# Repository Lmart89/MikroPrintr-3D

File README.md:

# MikroPrinter-3D.
## Una placa controladora de impresion 3d de bajo coste basada en Arduino.

## 💡 Origen del Concepto

Mikropintr es el resultado propio de ideas tomadas de proyectos como Sinaptec (https://reprap.org/wiki/SinapTec), Morpheus (https://github.com/pscrespo/Morpheus-STM32) entre otros que ofrecen una solucion compacta y de bajo coste para la construccion de una placa controladora de impresion 3D. Sin embargo el gran limitante de estas placas es la necesidad de modificar el firmware para lograr compatiblidad con estos dispositovos, algo que requiere de mucho trabajo mas alla de la personalizacion, sin contar con los bugs resultantes en el proceso.
MikroPrintr pretende ofrecer una solucion asequible, a la vez de ser 100% compatible con Marlin, permitiendo desarrollar todo el potencial y la personalizacion a gusto. Para quepueda ser una placa compacta se opto por el arduino mega 2560 pro, una version reducida de Arduino Mega.

## :heavy_check_mark: Características de MikroPrintr.

- MCU: Arduino Mega 2560 Pro-Micro. Un Arduino Mega reducido en tamaño.

- Soporte Estándar de Marlin 2.0

- Diseñada bajo el standar RAMPS 1.4.

- Fabricación para uso de componentes THT (Trough Hole). 

- Tamaño Reducido. 103 mm x 90mm. a 1 sola capa, o producir a dos capas si se desea.

- Soporte Estándar de la smart reprap controller (lcd 2004) o la smart reprap full graphic controller (lcd 12864). no necesita la placa adaptadora para la conexion.
  
- Soporte para Módulo Wifi (esp8266-01 o esp8266-01s) Se recomienda la versión Esp-01s. se requiere un regulador de nivel lógico de 5v a 3.3V.

## :chart_with_upwards_trend: Estado del Proyecto.

:construction: Proyecto en construcción :construction:

## :books: Registro de cambios

###  Abril 2025.
- Se optimizo el diseño de la placa, y se corrigieron algunos detalles menores de la circuiteria.
- Rediseño de las piezas de la impresora con nuevas medidas, por un error de medicion en algunas de ellas.
- se libera la version 1H. de la placa.  

## :books: Recursos adicionales.

los siguientes modelos de impresoras pueden dar una fuente de inspiracion para el montaje  o diseño de una impresora 3d. uselos segun discrecion y precaucion propias.

### Me Mini 3d Printer - la mas completa y compleja.

:earth_americas: link oficial. https://www.thingiverse.com/thing:5140212. 

### Skylab2 - una construccion sencilla y simple, recomendada para empezar. 

:earth_americas: link oficial. https://www.thingiverse.com/thing:4624533.

### Prusa mini- la version mini de la prusa i3.
   Requiere la mayoria de sus piezas en ABS. 

🌎 sitio oficial: https://www.printables.com/es/model/57214-mini-printable-parts/files

los archivos stl de estos modelos se encuentran en la carpeta "printable parts".

## :hammer_and_pick: Proyectos en conjunto. 
De momento estoy trabajando en el desarrollo de un software host propio para manejar la placa.

Si te interesa mi proyecto y deseas colaborar en el desarrollo, puedes contactarme, dejandome un mensaje o un request o solicitud de cambio via github.

Deseo que este proyecto pueda ser de utilidad para ti, maker. con :heart: desde Colombia 🇨🇴 para el mundo 🌎. :smile:

### <h4> :heavy_exclamation_mark: al hacer uso de los archivos publicados en este repositorio, el usuario acepta y asume su propia responsabilidad y riesgo por el uso y/o manipulacion de los archivos ofrecidos en este repositorio. :heavy_exclamation_mark: </h>

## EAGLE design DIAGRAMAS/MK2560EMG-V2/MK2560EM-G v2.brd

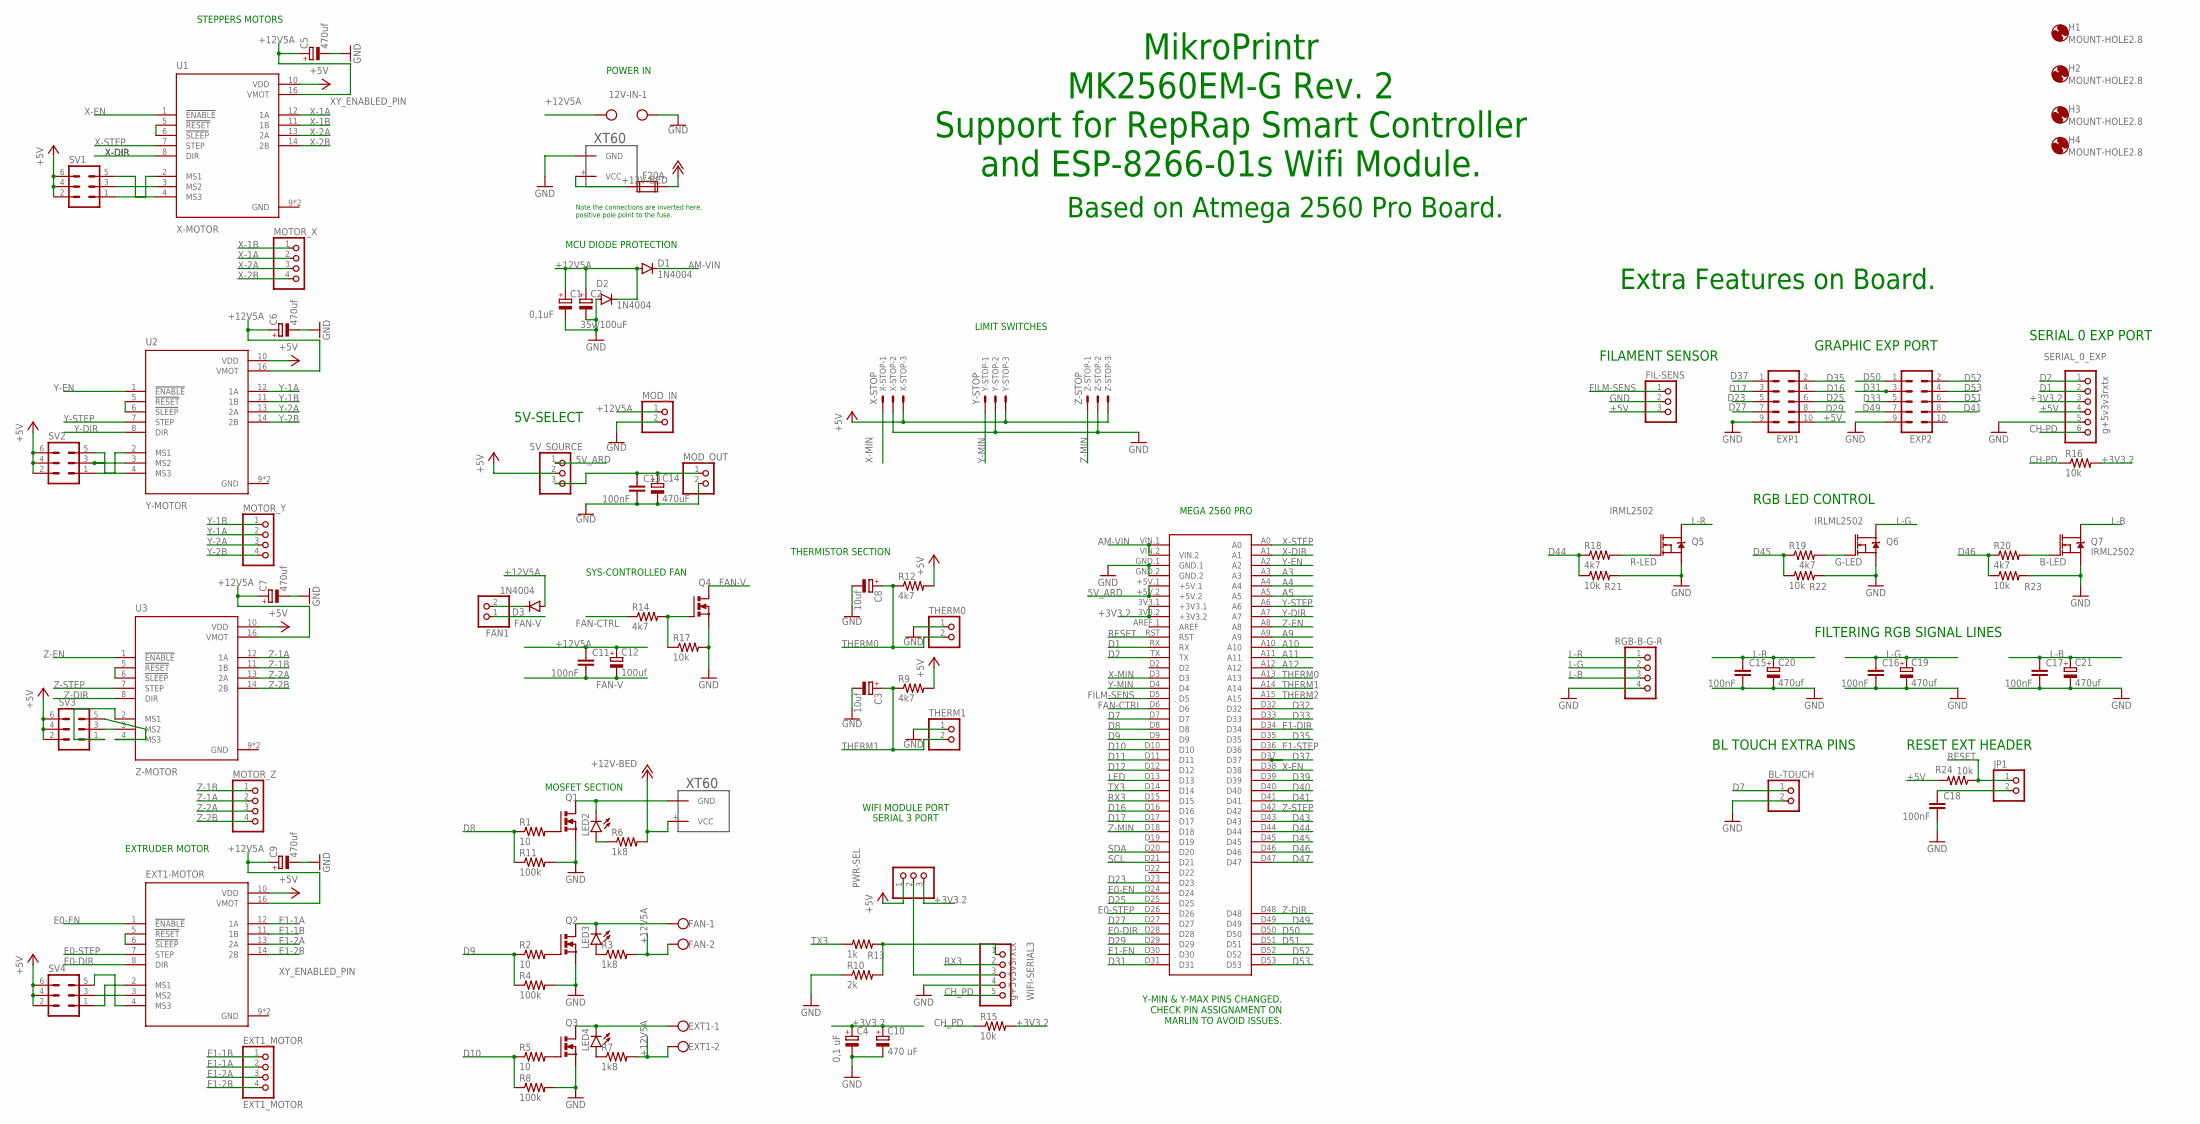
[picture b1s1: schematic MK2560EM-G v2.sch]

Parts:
5V_SOURCE: PINHD-1X3; 1X03
12V-IN: W237-102
ARD-MEGA: MEGA2560_MIKRO
BL-TOUCH: PINHD-1X2; 1X02
C1: 0,1uF; E2,5-5
C2: 35v/100uF; E2,5-5
C3, C8: 10uf; E2,5-6
C4: 0,1 uF; E2,5-5
C5, C6, C7, C9, C19, C20, C21: 470uf; E2,5-6E
C10: 470 uF; E2,5-5
C11, C13, C15, C16, C17, C18: 100nF; C2.5-2
C12: 100uf; E2,5-6
C14: 470uF; E2,5-6
D1, D2, D3: 1N4004; DO41-10
EXP1, EXP2: MA05-2
EXT1: W237-102
EXT1-MOTOR: A4988_STEPPER_MOTOR_DRIVER_CARRIER; MODULE_A4988_STEPPER_MOTOR_DRIVER_CARRIER
EXT1_MOTOR: EXT1_MOTOR; 1X04
F20A: FUSE2P; FUSE1
FAN: W237-102
FAN1: PINHD-1X2; 1X02
FIL-SENS: PINHD-1X3; 1X03
H1, H2, H3, H4: MOUNT-HOLE2.8; 2,8
JP1: PINHD-1X2; 1X02
LED2, LED3, LED4: LED3MM
MOD_IN: PINHD-1X2; 1X02
MOD_OUT: PINHD-1X2; 1X02
MOTOR_X: PINHD-1X4; 1X04
MOTOR_Y: PINHD-1X4; 1X04
MOTOR_Z: PINHD-1X4; 1X04
PWR-SEL: PINHD-1X3; 1X03
Q1, Q2, Q3, Q4: PMOSFET_NTO220BV; TO220BV
Q5, Q7: IRML2502; SOT23-3
Q6: IRLML2502; SOT23-3
R1, R2, R5: 10; 0204/7
R3, R6, R7: 1k8; 0204/7
R4, R8, R11: 100k; 0204/7
R9, R12, R14, R18, R19, R20: 4k7; 0204/7
R10: 2k; 0204/7
R13: 1k; 0204/7
R15, R16, R17, R21, R22, R23, R24: 10k; 0204/7
RGB-B-G-R: PINHD-1X4; 1X04
SERIAL_0_EXP: g+5v3v3rxtx; 1X06
SV1, SV2, SV3, SV4: MA03-2
THERM0, THERM1: PINHD-1X2; 1X02
U1: X-MOTOR; MODULE_A4988_STEPPER_MOTOR_DRIVER_CARRIER
U2: Y-MOTOR; MODULE_A4988_STEPPER_MOTOR_DRIVER_CARRIER
U3: Z-MOTOR; MODULE_A4988_STEPPER_MOTOR_DRIVER_CARRIER
U$1, U$2: XT60
WIFI-SERIAL3: g+5v3v3rxtx; 1X05
X-STOP: X-STOP; 22-23-2031
Y-STOP: Y-STOP; 22-23-2031
Z-STOP: Z-STOP; 22-23-2031

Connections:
5V_ARD: 5V_SOURCE.1, ARD-MEGA.+5V.1, ARD-MEGA.+5V.2
+3V3.2: ARD-MEGA.3V3.1 (+3V3.1), ARD-MEGA.3V3.2 (+3V3.2), C4.+, C10.+, PWR-SEL.3, R15.2, R16.2, SERIAL_0_EXP.3
+5V: 5V_SOURCE.2, EXP1.10, EXT1-MOTOR.10 (VDD), FIL-SENS.3, PWR-SEL.1, R9.2, R12.2, R24.2, SERIAL_0_EXP.4, SV1.2, SV1.4, SV1.6, SV2.2, SV2.4, SV2.6, SV3.2, SV3.4, SV3.6, SV4.2, SV4.4, SV4.6, U1.10 (VDD), U2.10 (VDD), U3.10 (VDD), X-STOP.3, Y-STOP.3, Z-STOP.3
+12V: F20A.2A, R6.2, U$2.+ (VCC)
+12V5A: 12V-IN.2, C1.+, C2.+, C5.+, C6.+, C7.+, C9.+, C11.1, C12.+, D1.A, D2.C, D3.A, EXT1.2, EXT1-MOTOR.16 (VMOT), FAN.2, MOD_IN.1, R3.2, R7.2, U1.16 (VMOT), U2.16 (VMOT), U3.16 (VMOT)
A3: ARD-MEGA.A3
A4: ARD-MEGA.A4
A5: ARD-MEGA.A5
A9: ARD-MEGA.A9
A10: ARD-MEGA.A10
A11: ARD-MEGA.A11
A12: ARD-MEGA.A12
AM-VIN: ARD-MEGA.VIN.1, ARD-MEGA.VIN.2, D1.C
B-LED: Q7.1 (G), R20.2
CH-PD: R16.1, SERIAL_0_EXP.6
CH_PD: R15.1, WIFI-SERIAL3.5
D1: ARD-MEGA.RX, SERIAL_0_EXP.2
D2: ARD-MEGA.TX, SERIAL_0_EXP.1
D7: ARD-MEGA.D7, BL-TOUCH.1
D8: ARD-MEGA.D8, R1.1, R11.1
D9: ARD-MEGA.D9, R2.1, R4.1
D10: ARD-MEGA.D10, R5.1, R8.1
D11: ARD-MEGA.D11
D12: ARD-MEGA.D12
D16: ARD-MEGA.D16, EXP1.4
D17: ARD-MEGA.D17, EXP1.3
D23: ARD-MEGA.D23, EXP1.5
D25: ARD-MEGA.D25, EXP1.6
D27: ARD-MEGA.D27, EXP1.7
D29: ARD-MEGA.D29, EXP1.8
D31: ARD-MEGA.D31, EXP2.3
D32: ARD-MEGA.D32
D33: ARD-MEGA.D33, EXP2.5
D35: ARD-MEGA.D35, EXP1.2
D37: ARD-MEGA.D37, EXP1.1
D39: ARD-MEGA.D39
D40: ARD-MEGA.D40
D41: ARD-MEGA.D41, EXP2.8
D43: ARD-MEGA.D43
D44: ARD-MEGA.D44, R18.1, R21.1
D45: ARD-MEGA.D45, R19.1, R22.1
D46: ARD-MEGA.D46, R20.1, R23.1
D47: ARD-MEGA.D47
D49: ARD-MEGA.D49, EXP2.7
D50: ARD-MEGA.D50, EXP2.1
D51: ARD-MEGA.D51, EXP2.6
D52: ARD-MEGA.D52, EXP2.2
D53: ARD-MEGA.D53, EXP2.4
E0-DIR: ARD-MEGA.D28, EXT1-MOTOR.8 (DIR)
E0-EN: ARD-MEGA.D24, EXT1-MOTOR.1 (!ENABLE)
E0-STEP: ARD-MEGA.D26, EXT1-MOTOR.7 (STEP)
E1-1A: EXT1-MOTOR.12 (1A), EXT1_MOTOR.2
E1-1B: EXT1-MOTOR.11 (1B), EXT1_MOTOR.1
E1-2A: EXT1-MOTOR.13 (2A), EXT1_MOTOR.3
E1-2B: EXT1-MOTOR.14 (2B), EXT1_MOTOR.4
E1-DIR: ARD-MEGA.D34
E1-EN: ARD-MEGA.D30
E1-STEP: ARD-MEGA.D36
FAN-CTRL: ARD-MEGA.D6, R14.1
FAN-V: C11.2, C12.-, FAN1.1, Q4.D
FILM-SENS: ARD-MEGA.D5, FIL-SENS.1
G-LED: Q6.1 (G), R19.2
GND: 12V-IN.1, ARD-MEGA.GND.1, ARD-MEGA.GND.2, BL-TOUCH.2, C1.-, C2.-, C3.-, C4.-, C5.-, C6.-, C7.-, C8.-, C9.-, C10.-, C13.2, C14.-, C15.2, C16.2, C17.2, C18.2, C19.-, C20.-, C21.-, D2.A, EXP1.9, EXP2.9, EXT1-MOTOR.9 (GND), EXT1-MOTOR.15 (GND), FIL-SENS.2, MOD_IN.2, MOD_OUT.2, Q1.S, Q2.S, Q3.S, Q4.S, Q5.2 (S), Q6.2 (S), Q7.2 (S), R4.2, R8.2, R10.1, R11.2, R17.2, R21.2, R22.2, R23.2, RGB-B-G-R.4, SERIAL_0_EXP.5, THERM0.1, THERM1.1, U1.9 (GND), U1.15 (GND), U2.9 (GND), U2.15 (GND), U3.9 (GND), U3.15 (GND), U$1.- (GND), WIFI-SERIAL3.4, X-STOP.2, Y-STOP.2, Z-STOP.2
L-B: C17.1, C21.+, Q7.3 (D), RGB-B-G-R.3
L-G: C16.1, C19.+, Q6.3 (D), RGB-B-G-R.2
L-R: C15.1, C20.+, Q5.3 (D), RGB-B-G-R.1
LED: ARD-MEGA.D13
unnamed: Q2.G, R2.2
unnamed: FAN.1, LED3.K (C), Q2.D
unnamed: LED3.A, R3.1
unnamed: Q3.G, R5.2
unnamed: EXT1.1, LED4.K (C), Q3.D
unnamed: LED4.A, R7.1
unnamed: LED2.K (C), Q1.D, U$2.- (GND)
unnamed: LED2.A, R6.1
unnamed: SV1.5, U1.4 (MS3)
unnamed: SV1.3, U1.3 (MS2)
unnamed: SV1.1, U1.2 (MS1)
unnamed: U2.5 (!RESET), U2.6 (!SLEEP)
unnamed: U1.5 (!RESET), U1.6 (!SLEEP)
unnamed: SV2.1, U2.2 (MS1)
unnamed: SV2.3, U2.3 (MS2)
unnamed: SV2.5, U2.4 (MS3)
unnamed: U3.5 (!RESET), U3.6 (!SLEEP)
unnamed: R10.2, R13.2, WIFI-SERIAL3.1
unnamed: SV3.3, U3.3 (MS2)
unnamed: Q1.G, R1.2
unnamed: SV3.1, U3.2 (MS1)
unnamed: SV3.5, U3.4 (MS3)
unnamed: EXT1-MOTOR.5 (!RESET), EXT1-MOTOR.6 (!SLEEP)
unnamed: EXT1-MOTOR.3 (MS2), SV4.3
unnamed: EXT1-MOTOR.4 (MS3), SV4.5
unnamed: EXT1-MOTOR.2 (MS1), SV4.1
unnamed: Q4.G, R14.2, R17.1
unnamed: D3.C, FAN1.2
unnamed: F20A.1A, U$1.+ (VCC)
unnamed: 5V_SOURCE.3, C13.1, C14.+, MOD_OUT.1
unnamed: PWR-SEL.2, WIFI-SERIAL3.3
unnamed: C18.1, JP1.2
R-LED: Q5.1 (G), R18.2
RESET: ARD-MEGA.RST, JP1.1, R24.1
RX3: ARD-MEGA.D15, WIFI-SERIAL3.2
SCL: ARD-MEGA.D21
SDA: ARD-MEGA.D20
THERM0: ARD-MEGA.A13, C8.+, R12.1, THERM0.2
THERM1: ARD-MEGA.A14, C3.+, R9.1, THERM1.2
THERM2: ARD-MEGA.A15
TX3: ARD-MEGA.D14, R13.1
X-1A: MOTOR_X.2, U1.12 (1A)
X-1B: MOTOR_X.1, U1.11 (1B)
X-2A: MOTOR_X.3, U1.13 (2A)
X-2B: MOTOR_X.4, U1.14 (2B)
X-DIR: ARD-MEGA.A1, U1.8 (DIR)
X-EN: ARD-MEGA.D38, U1.1 (!ENABLE)
X-MIN: ARD-MEGA.D3, X-STOP.1
X-STEP: ARD-MEGA.A0, U1.7 (STEP)
Y-1A: MOTOR_Y.2, U2.12 (1A)
Y-1B: MOTOR_Y.1, U2.11 (1B)
Y-2A: MOTOR_Y.3, U2.13 (2A)
Y-2B: MOTOR_Y.4, U2.14 (2B)
Y-DIR: ARD-MEGA.A7, U2.8 (DIR)
Y-EN: ARD-MEGA.A2, U2.1 (!ENABLE)
Y-MIN: ARD-MEGA.D4, Y-STOP.1
Y-STEP: ARD-MEGA.A6, U2.7 (STEP)
Z-1A: MOTOR_Z.2, U3.12 (1A)
Z-1B: MOTOR_Z.1, U3.11 (1B)
Z-2A: MOTOR_Z.3, U3.13 (2A)
Z-2B: MOTOR_Z.4, U3.14 (2B)
Z-DIR: ARD-MEGA.D48, U3.8 (DIR)
Z-EN: ARD-MEGA.A8, U3.1 (!ENABLE)
Z-MIN: ARD-MEGA.D18, Z-STOP.1
Z-STEP: ARD-MEGA.D42, U3.7 (STEP)

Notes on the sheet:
MikroPrintr MK2560EM-G Rev. 2 Support for RepRap Smart Controller and ESP-8266-01s Wifi Module.
Based on Atmega 2560 Pro Board.
Note the connections are inverted here. positive pole point to the fuse.
MCU DIODE PROTECTION
MOSFET SECTION
THERMISTOR SECTION
GRAPHIC EXP PORT
MEGA 2560 PRO
WIFI MODULE PORT
STEPPERS MOTORS
EXTRUDER MOTOR
LIMIT SWITCHES
SYS-CONTROLLED FAN
POWER IN
Y-MIN & Y-MAX PINS CHANGED. CHECK PIN ASSIGNAMENT ON MARLIN TO AVOID ISSUES.
5V-SELECT
SERIAL 3 PORT
SERIAL 0 EXP PORT
Extra Features on Board.
RGB LED CONTROL
FILTERING RGB SIGNAL LINES
FILAMENT SENSOR
RESET EXT HEADER
BL TOUCH EXTRA PINS

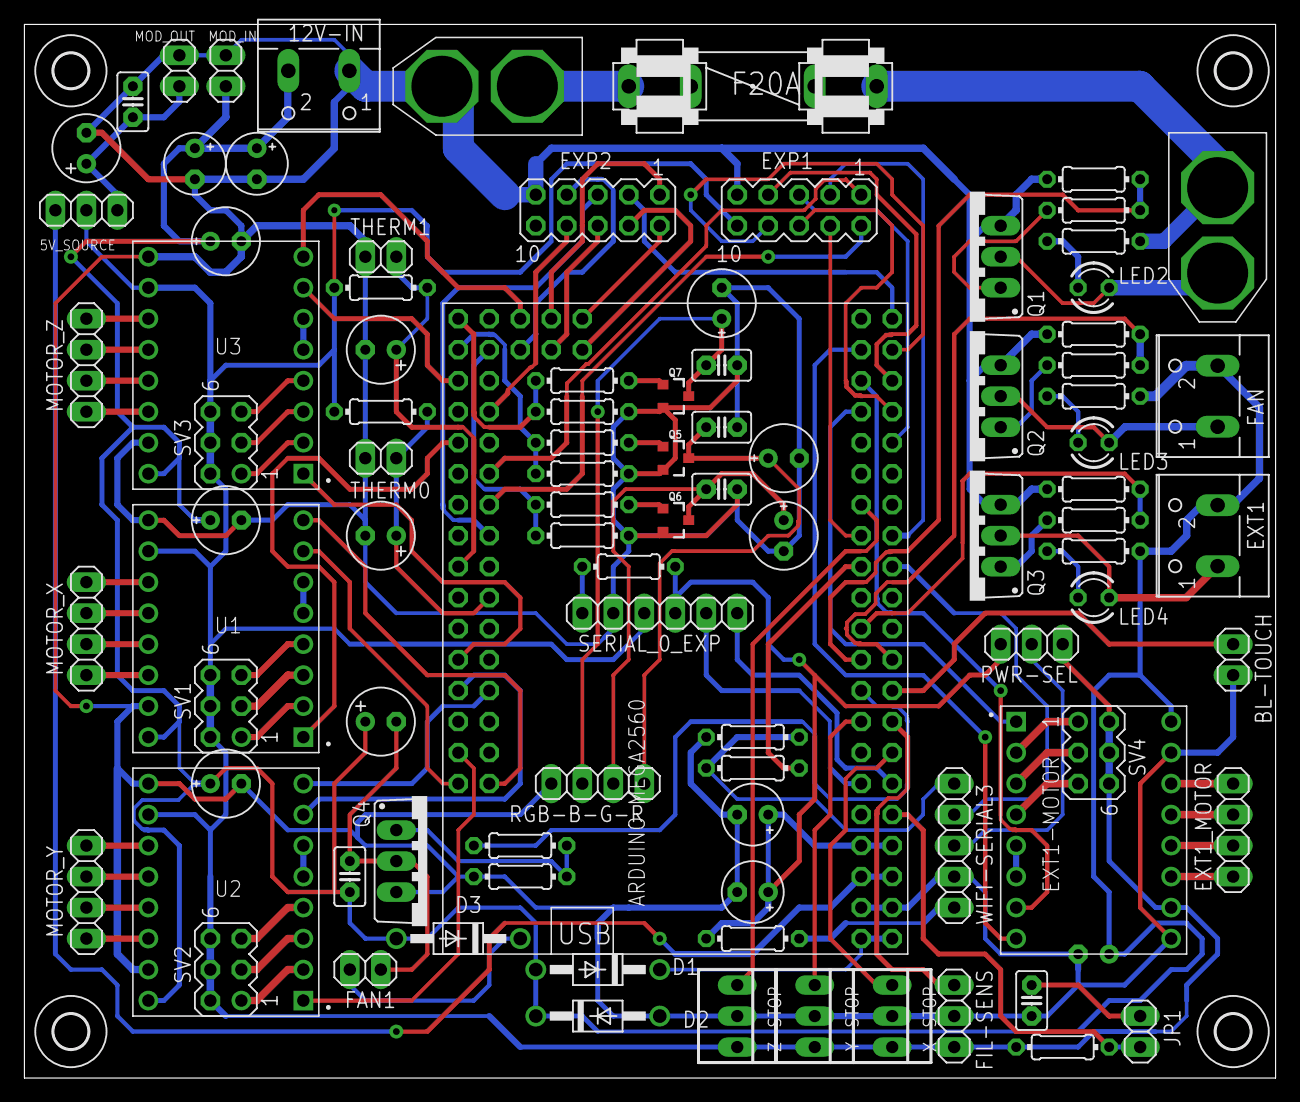
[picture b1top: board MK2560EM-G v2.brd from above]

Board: 2 copper layers, 102.5 x 86.4 mm, 99 parts (1 on the bottom side), 111 nets.

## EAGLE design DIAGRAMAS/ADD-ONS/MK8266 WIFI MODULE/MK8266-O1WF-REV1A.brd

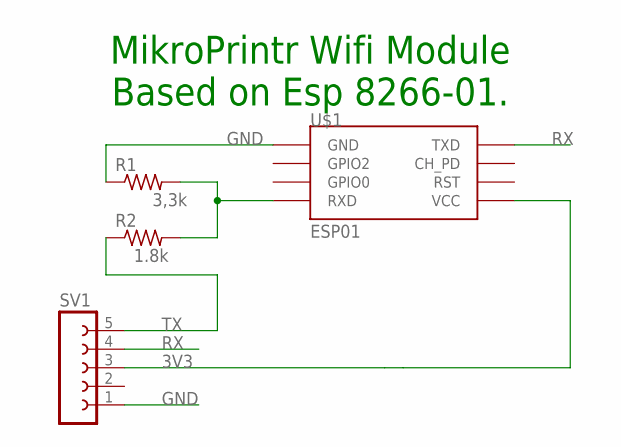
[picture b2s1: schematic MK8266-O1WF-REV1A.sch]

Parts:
R1: 3,3k; 0204/7
R2: 1.8k; 0204/7
SV1: FE05-1
U$1: ESP01

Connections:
3V3: SV1.3, U$1.VCC
GND: R1.1, SV1.1, U$1.GND
unnamed: R1.2, R2.2, U$1.RX (RXD)
RX: SV1.4, U$1.TX (TXD)
TX: R2.1, SV1.5

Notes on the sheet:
MikroPrintr Wifi Module Based on Esp 8266-01.

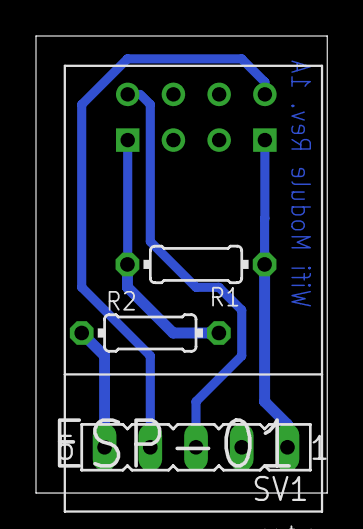
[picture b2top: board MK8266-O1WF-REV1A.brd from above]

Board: 2 copper layers, 16.2 x 25.4 mm, 4 parts (0 on the bottom side), 5 nets.

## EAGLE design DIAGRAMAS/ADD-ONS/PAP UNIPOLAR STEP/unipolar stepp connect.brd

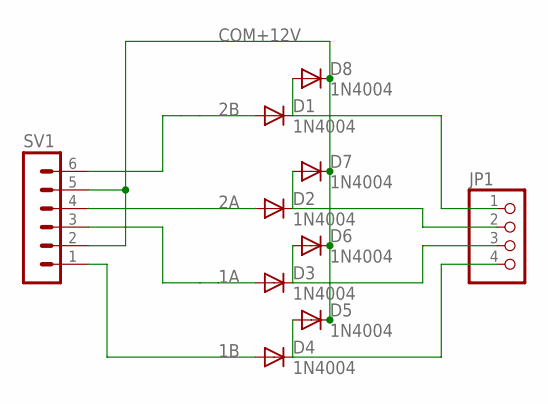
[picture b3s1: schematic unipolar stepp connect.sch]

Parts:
D1, D2, D3, D4, D5, D6, D7, D8: 1N4004; DO41-10
JP1: PINHD-1X4/90; 1X04/90
SV1: MA06-1

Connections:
1A: D3.A, SV1.3
1B: D4.A, SV1.1
2A: D2.A, SV1.4
2B: D1.A, SV1.6
COM+12V: D5.C, D6.C, D7.C, D8.C, SV1.2, SV1.5
unnamed: D1.C, D8.A, JP1.1
unnamed: D2.C, D7.A, JP1.2
unnamed: D3.C, D6.A, JP1.3
unnamed: D4.C, D5.A, JP1.4

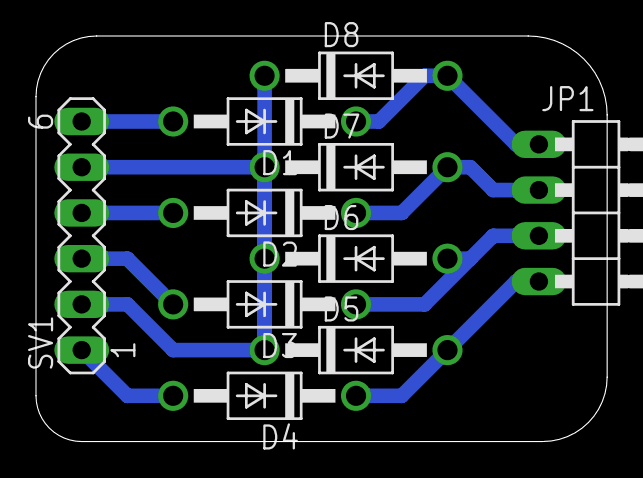
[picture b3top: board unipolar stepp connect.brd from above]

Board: 2 copper layers, 31.7 x 22.5 mm, 10 parts (0 on the bottom side), 9 nets.

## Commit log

2023-07-06 Actualización README.md
    actualización de la información del repositorio en el archivo README.
2023-07-06 Actualizar README.md
2023-07-06 Actualizar README.md
    actualización de README.
2023-07-06 Printable parts models
    añadido de la primera variante para las partes imprimibles en 3d.
2023-07-06 DIAGRAMAS
    nuevos diagramas añadidos
2023-07-06 main pcb controller
    añadida placa principal pcb.
2023-07-06 NEW README FILE
    NEW README FILE.
2023-07-06 modelos 3d
    modelos 3d renderizados del aspecto final de la placa.
2023-07-11 new 3d variants
    nuevos modelos 3d para imprimir las partes plasticas.
2023-07-13 new renders and mods
    new 3d rendered pcb images, and also son minor modifications to the pcb layout.
2023-07-25 new pcb circuit files
    nuevos archivos pcb corregidos, y añadido un pcb a color con aambas caras.
2023-07-27 new pcb optimizations
    minor pcb error fixes and optimizations.
    -changed some thermistors capacitors components for bigger ones.
    - added silkscreen pdf for soldering reference.
2023-08-05 Update README.md
    update info for repo readme file.
2023-08-09 Update README.md
    nuevo readme!
2023-08-10 new 3d rendered files
    new files update.
2023-08-10 Update README.md
    new readme update for a better info about the project
2023-08-11 Update README.md
    New readme update
2023-08-18 pcb fixes v1G.1
    - pcb bug corrections space clearance on x,y,z drivers resolution pin headers. changed for right pin headers.
    - changed F5A fuse for +12v rail, for aa short cylinder standard fuse.
    - pcb resized, for more space, and better alocation of components.
    -
2023-08-28 updated structure files
2023-09-12 updated new mikroprinter 3d parts
    added updated and new Mikroprinter 3D printable parts.
2025-03-27 Update README.md
    update info on readme file
2025-03-27 Update README.md
    actualizacion y optimizacion del readme
2025-04-05 Update README.md
    updated change log.
2025-04-05 md and update files
    new updated files uploaded.
2025-04-13 new parts uploaded!
    added new 3d parts!
2025-04-13 updated 3d files
    added new 3d files for printer parts
2025-04-25 new version released
    MK2560EMG V2 RELEASED.
    - new pcb redesign.
    - added new ports and components.
    - improve quality on routes and better use of space. retaining same form factor and siez.
2025-04-29 pcb minor fix
    - optimization and minor pcb fix for better design and perfomance.
2025-04-30 new pcb files
    - updated pcb and sch files!
    - new improvements and funcionality of the controller board.
2025-05-09 important pcb update
    - added XT60 connectors for bed connection.
    - optimization of some pcb tracks, added support for ext reset button.
2025-05-15 new pcb update and fixes
    - new pcb fixes and testing for factory pcb production.
    - added picture of pcb components in place.
    - added pdf with the final design of the pcb.
2025-05-15 firmware and host development.
    - added Marlin configuration files for compiling.
    - initial development of host software in python. it can change in the future.

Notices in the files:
parts and their libraries:
SparkFun-DiscreteSemi: Licensing: Creative Commons ShareAlike 4.0 International - https://creativecommons.org/licenses/by-sa/4.0
